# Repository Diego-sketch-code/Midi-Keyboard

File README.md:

# Midi-Keyboard
MIDI keypad (Something like a DJ SET

Midikeypad is an instrument with Sliders, rotary encoders, neopixels ,switches and capacitive touch with the form of a DJ set
My midi key pad is base on the design of the midikeypad of Kai Pereira only changes the order of the components and the shapes of the pads but i made it based on a DJ set because all the stuff that it uses remenber to me to DJ set
Components:
switches push
potentiometer
Neopixels
pads
rotatory encoder
Waveshare ESP32-S3-ZERO

this work by touching the pads ,this is because the pads have like an electric field and when you touch it your own electric field interferes with the one of the midikey 

i made this with the inspiration of make my own DJ set or something similar and have some interesting things in my hands also it help me to develop some new skills for future projects and make me reuse some skills that i learned in the past ones

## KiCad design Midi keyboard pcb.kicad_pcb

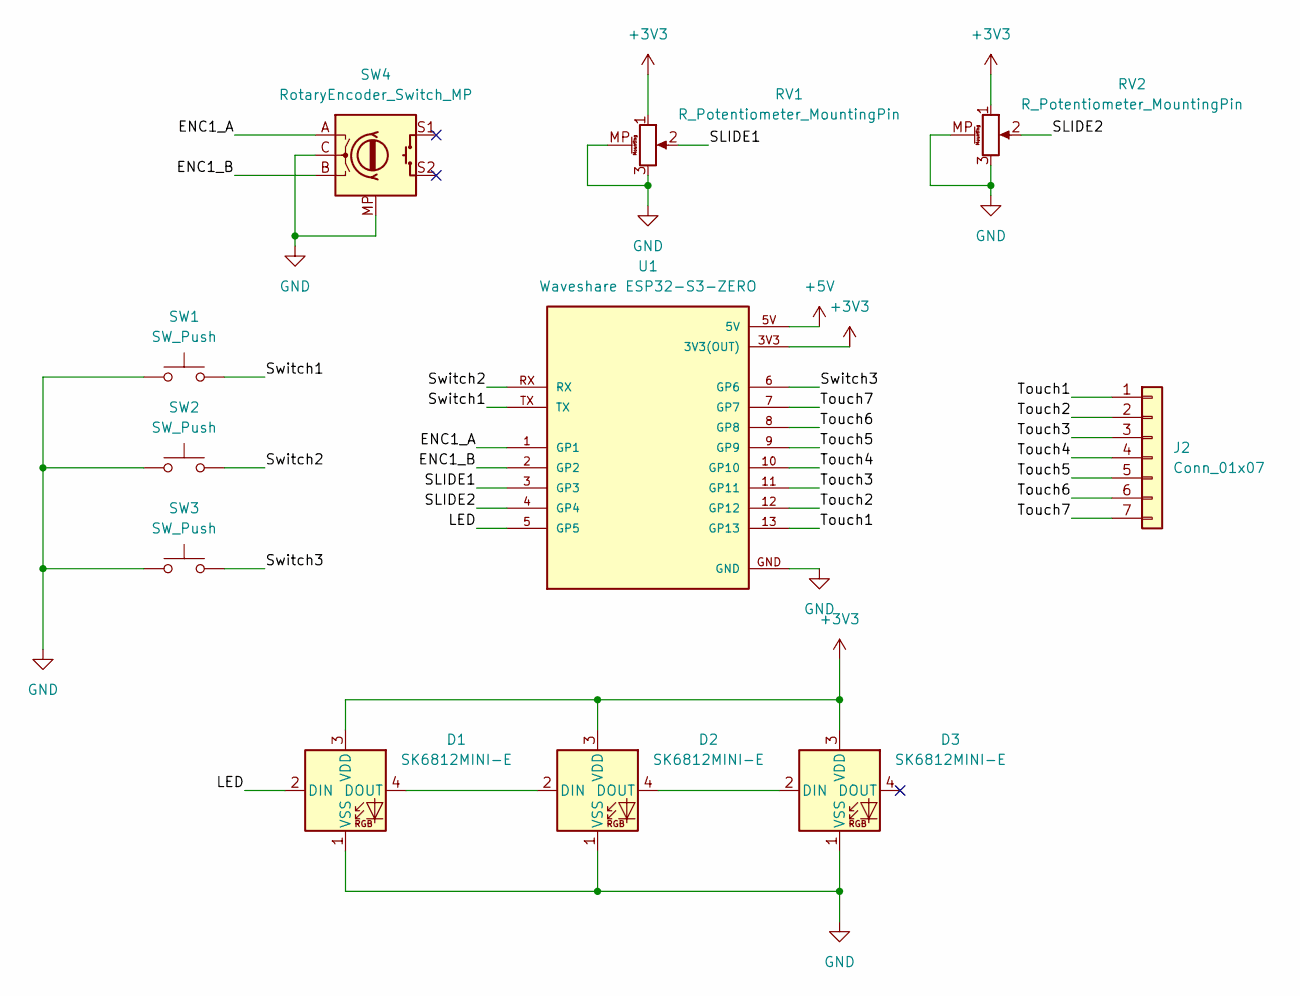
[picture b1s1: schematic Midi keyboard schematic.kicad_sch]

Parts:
D1, D2, D3: SK6812MINI-E; LED_SK6812MINI-E_3.2x2.8mm_P1.5mm_ReverseMount
J2: Conn_01x07; Pads
RV1, RV2: R_Potentiometer_MountingPin; Potentiometer_Bourns_PTA1543_Single_Slide
SW1, SW2, SW3: SW_Push; Kailh Choc Low-Profile Switches
SW4: RotaryEncoder_Switch_MP; RotaryEncoder_Alps_EC11E-Switch_Vertical_H20mm
U1: Waveshare ESP32-S3-ZERO; Waveshare ESP32-S3-Zero; PARTREV NA

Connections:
+3V3: D1.3 (VDD), D2.3 (VDD), D3.3 (VDD), RV1.1, RV2.1, U1.3V3 (3V3(OUT))
+5V: U1.5V
/ENC1_A: SW4.A, U1.1 (GP1)
/ENC1_B: SW4.B, U1.2 (GP2)
/LED: D1.2 (DIN), U1.5 (GP5)
/SLIDE1: RV1.2, U1.3 (GP3)
/SLIDE2: RV2.2, U1.4 (GP4)
/Switch1: SW1.2, U1.TX
/Switch2: SW2.2, U1.RX
/Switch3: SW3.2, U1.6 (GP6)
/Touch1: J2.1, U1.13 (GP13)
/Touch2: J2.2, U1.12 (GP12)
/Touch3: J2.3, U1.11 (GP11)
/Touch4: J2.4, U1.10 (GP10)
/Touch5: J2.5, U1.9 (GP9)
/Touch6: J2.6, U1.8 (GP8)
/Touch7: J2.7, U1.7 (GP7)
GND: D1.1 (VSS), D2.1 (VSS), D3.1 (VSS), RV1.3, RV1.MP (MountPin), RV2.3, RV2.MP (MountPin), SW1.1, SW2.1, SW3.1, SW4.C, SW4.MP, U1.GND
unnamed: D1.4 (DOUT), D2.2 (DIN)
unnamed: D2.4 (DOUT), D3.2 (DIN)

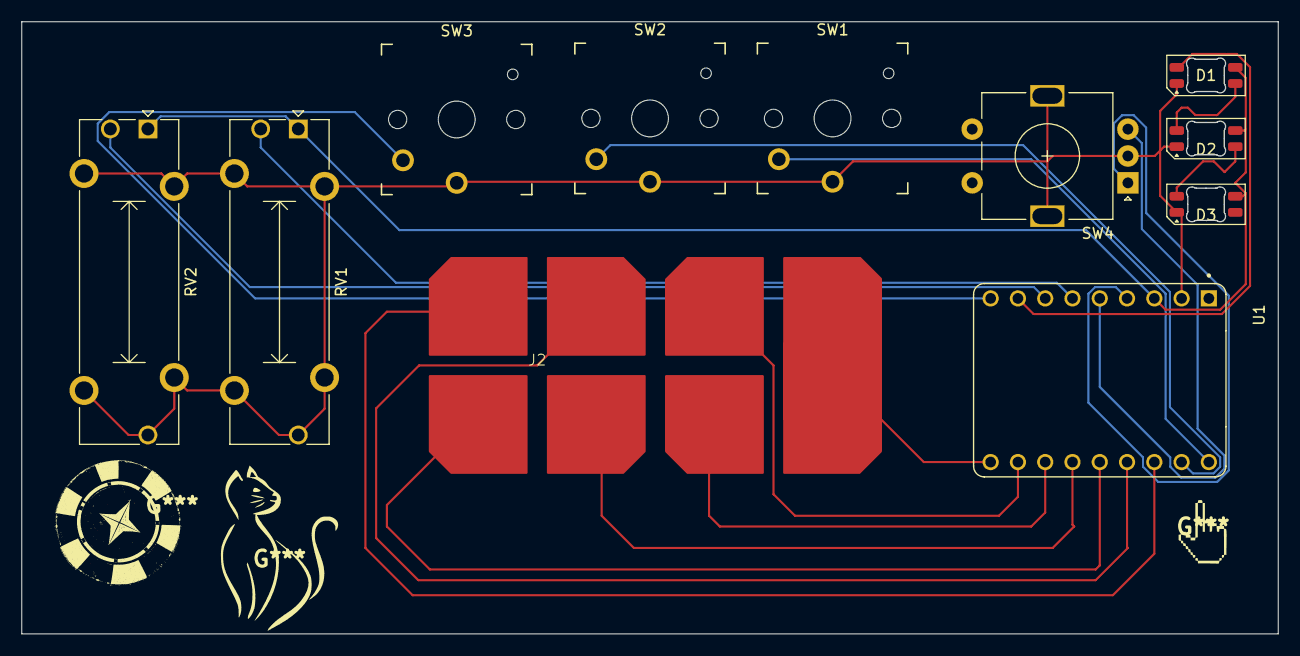
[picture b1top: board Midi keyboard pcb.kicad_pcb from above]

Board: 2 copper layers, 117.0 x 57.0 mm, 11 parts (0 on the bottom side), 19 nets.

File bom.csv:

Designator,Footprint,Quantity,Value,shop and link,Price,
"D1, D2, D3",LED_SK6812MINI-E_3.2x2.8mm_P1.5mm_ReverseMount,3,SK6812MINI-E,Tienda Shenzhen modular,$1.68,
J2,Pads,1,Conn_01x07,,,
"RV1, RV2",Potentiometer_Bourns_PTA1543_Single_Slide,2,R_Potentiometer_MountingPin,Guangzhou Donghong Ele,$3.74,
"SW1, SW2, SW3",Kailh Choc Low-Profile Switches,3,SW_Push,Yooya Store,$1.11,
SW4,RotaryEncoder_Alps_EC11E-Switch_Vertical_H20mm,1,RotaryEncoder_Switch_MP,Tienda Great BOBOT,$0.37,
U1,Waveshare ESP32-S3-Zero,1,Waveshare ESP32-S3-ZERO,NEW IGBT MODULE FUSE Store,$7.10,
